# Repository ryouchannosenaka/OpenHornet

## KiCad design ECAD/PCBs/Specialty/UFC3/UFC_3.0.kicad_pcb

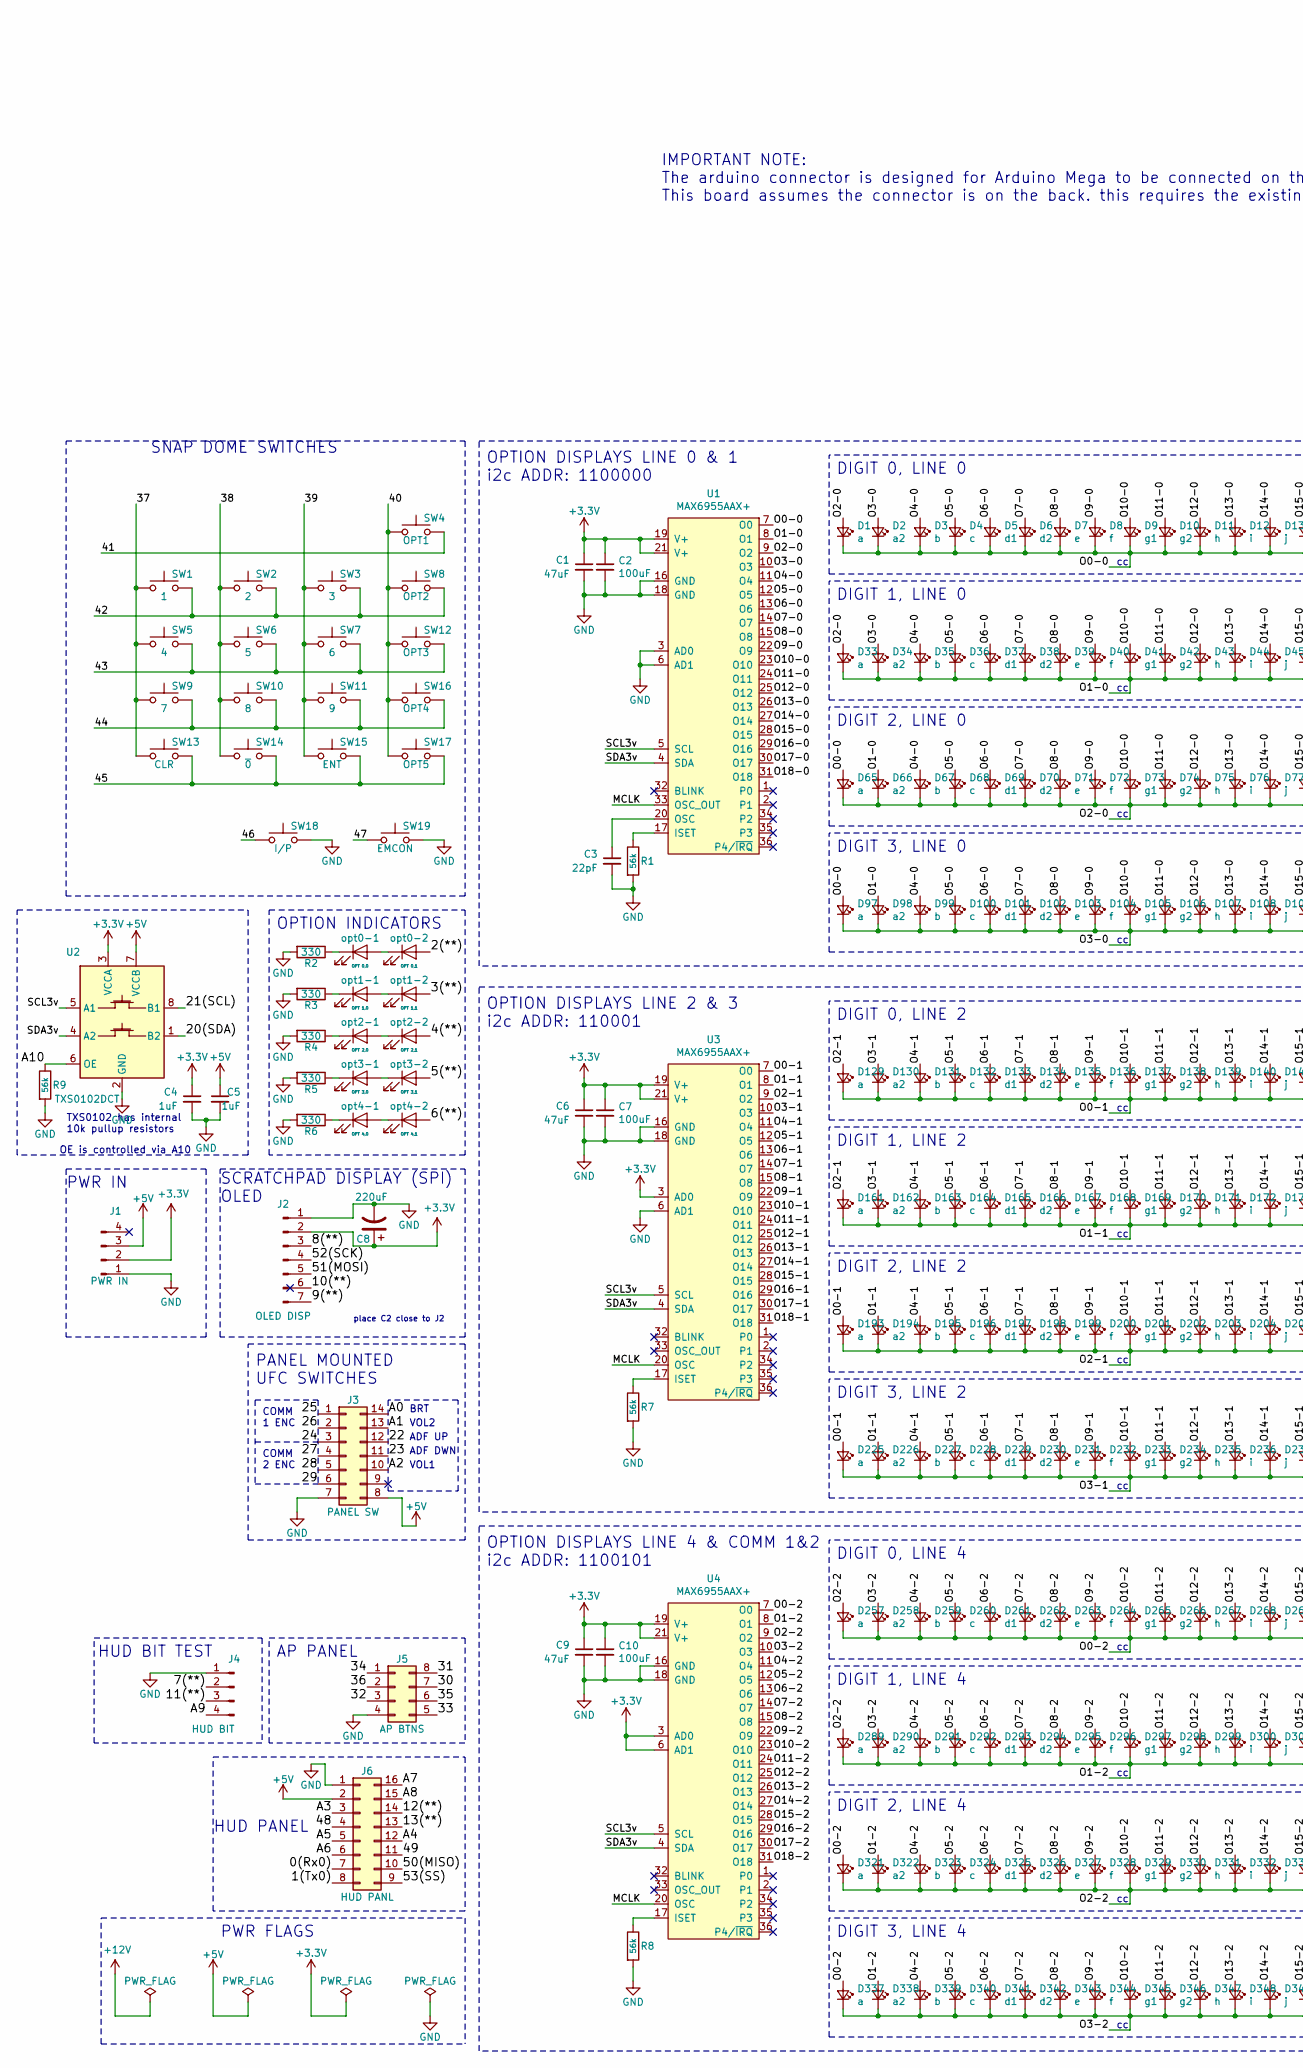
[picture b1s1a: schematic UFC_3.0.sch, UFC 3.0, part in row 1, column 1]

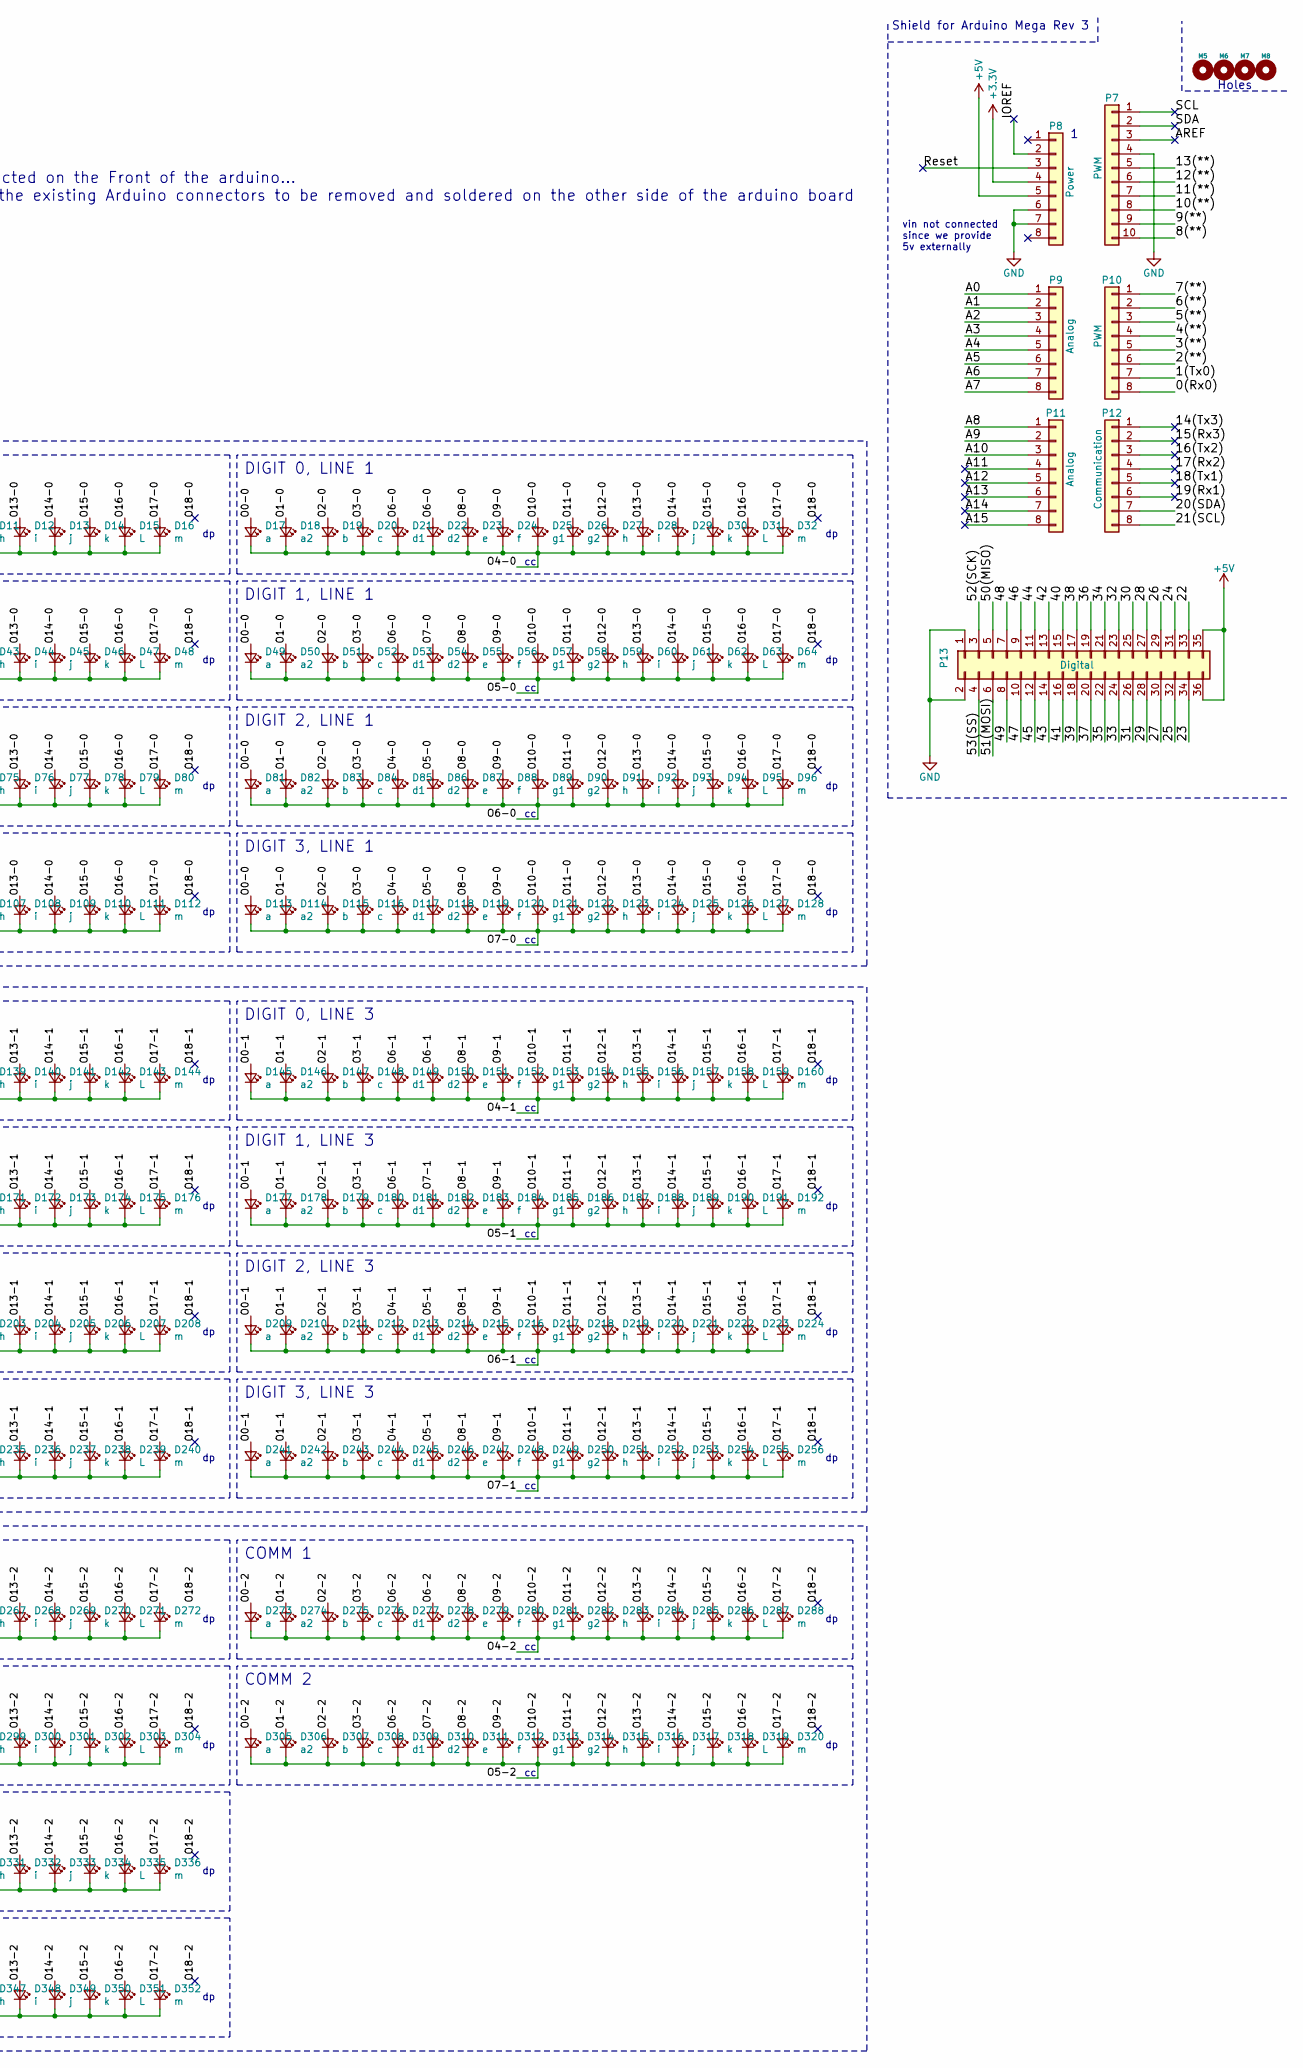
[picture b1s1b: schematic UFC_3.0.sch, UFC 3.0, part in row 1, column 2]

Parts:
C1, C6, C9: 47uF; C_1206_3216Metric
C2, C7, C10: 100uF; C_1206_3216Metric
C3: 22pF; C_0402_1005Metric
C4, C5: 1uF; C_0402_1005Metric
C8: 220uF; CP_Elec_6.3x7.7
D1, D17, D33, D49, D65, D81, D97, D113, D129, D145, D161, D177, D193, D209, D225, D241, D257, D273, D289, D305, D321, D337: a; LED_0402_1005Metric
D2, D18, D34, D50, D66, D82, D98, D114, D130, D146, D162, D178, D194, D210, D226, D242, D258, D274, D290, D306, D322, D338: a2; LED_0402_1005Metric
D3, D19, D35, D51, D67, D83, D99, D115, D131, D147, D163, D179, D195, D211, D227, D243, D259, D275, D291, D307, D323, D339: b; LED_0402_1005Metric
D4, D20, D36, D52, D68, D84, D100, D116, D132, D148, D164, D180, D196, D212, D228, D244, D260, D276, D292, D308, D324, D340: c; LED_0402_1005Metric
D5, D21, D37, D53, D69, D85, D101, D117, D133, D149, D165, D181, D197, D213, D229, D245, D261, D277, D293, D309, D325, D341: d1; LED_0402_1005Metric
D6, D22, D38, D54, D70, D86, D102, D118, D134, D150, D166, D182, D198, D214, D230, D246, D262, D278, D294, D310, D326, D342: d2; LED_0402_1005Metric
D7, D23, D39, D55, D71, D87, D103, D119, D135, D151, D167, D183, D199, D215, D231, D247, D263, D279, D295, D311, D327, D343: e; LED_0402_1005Metric
D8, D24, D40, D56, D72, D88, D104, D120, D136, D152, D168, D184, D200, D216, D232, D248, D264, D280, D296, D312, D328, D344: f; LED_0402_1005Metric
D9, D25, D41, D57, D73, D89, D105, D121, D137, D153, D169, D185, D201, D217, D233, D249, D265, D281, D297, D313, D329, D345: g1; LED_0402_1005Metric
D10, D26, D42, D58, D74, D90, D106, D122, D138, D154, D170, D186, D202, D218, D234, D250, D266, D282, D298, D314, D330, D346: g2; LED_0402_1005Metric
D11, D27, D43, D59, D75, D91, D107, D123, D139, D155, D171, D187, D203, D219, D235, D251, D267, D283, D299, D315, D331, D347: h; LED_0402_1005Metric
D12, D28, D44, D60, D76, D92, D108, D124, D140, D156, D172, D188, D204, D220, D236, D252, D268, D284, D300, D316, D332, D348: i; LED_0402_1005Metric
D13, D29, D45, D61, D77, D93, D109, D125, D141, D157, D173, D189, D205, D221, D237, D253, D269, D285, D301, D317, D333, D349: j; LED_0402_1005Metric
D14, D30, D46, D62, D78, D94, D110, D126, D142, D158, D174, D190, D206, D222, D238, D254, D270, D286, D302, D318, D334, D350: k; LED_0402_1005Metric
D15, D31, D47, D63, D79, D95, D111, D127, D143, D159, D175, D191, D207, D223, D239, D255, D271, D287, D303, D319, D335, D351: L; LED_0402_1005Metric
D16, D32, D48, D64, D80, D96, D112, D128, D144, D160, D176, D192, D208, D224, D240, D256, D272, D288, D304, D320, D336, D352: m; LED_0402_1005Metric
J1: PWR IN; PinHeader_1x04_P2.54mm_Vertical_SMD_Pin1Left
J2: OLED DISP; PinHeader_1x07_P2.54mm_Vertical_SMD_Pin1Left
J3: PANEL SW; PinHeader_2x07_P2.54mm_Vertical_SMD
J4: HUD BIT; PinHeader_1x04_P2.54mm_Vertical_SMD_Pin1Left
J5: AP BTNS; PinHeader_2x04_P2.54mm_Vertical_SMD
J6: HUD PANL; PinHeader_2x08_P2.54mm_Vertical_SMD
M5, M6, M7, M8: mounting hole; MountingHole_2.7mm_M2.5
P7: PWM; PinHeader_1x10_P2.54mm_Vertical_SMD_Pin1Left
P8: Power; PinHeader_1x08_P2.54mm_Vertical_SMD_Pin1Left
P9, P11: Analog; PinHeader_1x08_P2.54mm_Vertical_SMD_Pin1Left
P10: PWM; PinHeader_1x08_P2.54mm_Vertical_SMD_Pin1Left
P12: Communication; PinHeader_1x08_P2.54mm_Vertical_SMD_Pin1Left
P13: Digital; PinHeader_2x18_P2.54mm_Vertical_SMD
R1, R7, R8, R9: 56k; R_0402_1005Metric
R2, R3, R4, R5, R6: 330; R_0402_1005Metric
SW1: 1; SWITCH_SNAP_DOME
SW2: 2; SWITCH_SNAP_DOME
SW3: 3; SWITCH_SNAP_DOME
SW4: OPT1; SWITCH_SNAP_DOME
SW5: 4; SWITCH_SNAP_DOME
SW6: 5; SWITCH_SNAP_DOME
SW7: 6; SWITCH_SNAP_DOME
SW8: OPT2; SWITCH_SNAP_DOME
SW9: 7; SWITCH_SNAP_DOME
SW10: 8; SWITCH_SNAP_DOME
SW11: 9; SWITCH_SNAP_DOME
SW12: OPT3; SWITCH_SNAP_DOME
SW13: CLR; SWITCH_SNAP_DOME
SW14: ~0; SWITCH_SNAP_DOME
SW15: ENT; SWITCH_SNAP_DOME
SW16: OPT4; SWITCH_SNAP_DOME
SW17: OPT5; SWITCH_SNAP_DOME
SW18: I/P; SWITCH_SNAP_DOME
SW19: EMCON; SWITCH_SNAP_DOME
U1, U3, U4: MAX6955AAX+; SSOP-36
U2: TXS0102DCT; SSOP-8_2.95x2.8mm_P0.65mm
opt0-1: OPT 0,0; LED_0402_1005Metric
opt0-2: OPT 0,1; LED_0402_1005Metric
opt1-1: OPT 1,0; LED_0402_1005Metric
opt1-2: OPT 1,1; LED_0402_1005Metric
opt2-1: OPT 2,0; LED_0402_1005Metric
opt2-2: OPT 2,1; LED_0402_1005Metric
opt3-1: OPT 3,0; LED_0402_1005Metric
opt3-2: OPT 3,1; LED_0402_1005Metric
opt4-1: OPT 4,0; LED_0402_1005Metric
opt4-2: OPT 4,1; LED_0402_1005Metric

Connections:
+3V3: C1.1, C2.1, C4.1, C6.1, C7.1, C8.1, C9.1, C10.1, J1.2, J2.2, P8.4, U1.19 (V+), U1.21 (V+), U2.3 (VCCA), U3.3 (AD0), U3.19 (V+), U3.21 (V+), U4.3 (AD0), U4.6 (AD1), U4.19 (V+), U4.21 (V+)
+5V: C5.1, J1.3, J3.8, J6.2, P8.5, P13.35, P13.36, U2.7 (VCCB)
/0(Rx0): J6.7, P10.8
/1(Tx0): J6.8, P10.7
/2(**): P10.6, opt0-2.2 (A)
/3(**): P10.5, opt1-2.2 (A)
/4(**): P10.4, opt2-2.2 (A)
/5(**): P10.3, opt3-2.2 (A)
/6(**): P10.2, opt4-2.2 (A)
/7(**): J4.2, P10.1
/8(**): J2.3, P7.10
/9(**): J2.7, P7.9
/10(**): J2.6, P7.8
/11(**): J4.3, P7.7
/12(**): J6.14, P7.6
/13(**): J6.13, P7.5
/14(Tx3): P12.1
/15(Rx3): P12.2
/16(Tx2): P12.3
/17(Rx2): P12.4
/18(Tx1): P12.5
/19(Rx1): P12.6
/20(SDA): P12.7, U2.1 (B2)
/21(SCL): P12.8, U2.8 (B1)
/22: J3.12, P13.33
/23: J3.11, P13.34
/24: J3.3, P13.31
/25: J3.1, P13.32
/26: J3.2, P13.29
/27: J3.4, P13.30
/28: J3.5, P13.27
/29: J3.6, P13.28
/30: J5.7, P13.25
/31: J5.8, P13.26
/32: J5.3, P13.23
/33: J5.5, P13.24
/34: J5.1, P13.21
/35: J5.6, P13.22
/36: J5.2, P13.19
/37: P13.20, SW1.1, SW5.1, SW9.1, SW13.1
/38: P13.17, SW2.1, SW6.1, SW10.1, SW14.1
/39: P13.18, SW3.1, SW7.1, SW11.1, SW15.1
/40: P13.15, SW4.1, SW8.1, SW12.1, SW16.1, SW17.1
/41: P13.16, SW4.2
/42: P13.13, SW1.2, SW2.2, SW3.2, SW8.2
/43: P13.14, SW5.2, SW6.2, SW7.2, SW12.2
/44: P13.11, SW9.2, SW10.2, SW11.2, SW16.2
/45: P13.12, SW13.2, SW14.2, SW15.2, SW17.2
/46: P13.9, SW18.1
/47: P13.10, SW19.1
/48: J6.4, P13.7
/49: J6.11, P13.8
/50(MISO): J6.10, P13.5
/51(MOSI): J2.5, P13.6
/52(SCK): J2.4, P13.3
/53(SS): J6.9, P13.4
/A0: J3.14, P9.1
/A1: J3.13, P9.2
/A2: J3.10, P9.3
/A3: J6.3, P9.4
/A4: J6.12, P9.5
/A5: J6.5, P9.6
/A6: J6.6, P9.7
/A7: J6.16, P9.8
/A8: J6.15, P11.1
/A9: J4.4, P11.2
/A10: P11.3, R9.1, U2.6 (OE)
/A11: P11.4
/A12: P11.5
/A13: P11.6
/A14: P11.7
/A15: P11.8
/AREF: P7.3
/IOREF: P8.2
/MCLK: U1.33 (OSC_OUT), U3.20 (OSC), U4.20 (OSC)
/O0-0: D1.1 (K), D2.1 (K), D3.1 (K), D4.1 (K), D5.1 (K), D6.1 (K), D7.1 (K), D8.1 (K), D9.1 (K), D10.1 (K), D11.1 (K), D12.1 (K), D13.1 (K), D14.1 (K), D15.1 (K), D16.1 (K), D17.2 (A), D49.2 (A), D65.2 (A), D81.2 (A), D97.2 (A), D113.2 (A), U1.7 (O0)
/O0-1: D129.1 (K), D130.1 (K), D131.1 (K), D132.1 (K), D133.1 (K), D134.1 (K), D135.1 (K), D136.1 (K), D137.1 (K), D138.1 (K), D139.1 (K), D140.1 (K), D141.1 (K), D142.1 (K), D143.1 (K), D144.1 (K), D145.2 (A), D177.2 (A), D193.2 (A), D209.2 (A), D225.2 (A), D241.2 (A), U3.7 (O0)
/O0-2: D257.1 (K), D258.1 (K), D259.1 (K), D260.1 (K), D261.1 (K), D262.1 (K), D263.1 (K), D264.1 (K), D265.1 (K), D266.1 (K), D267.1 (K), D268.1 (K), D269.1 (K), D270.1 (K), D271.1 (K), D272.1 (K), D273.2 (A), D305.2 (A), D321.2 (A), D337.2 (A), U4.7 (O0)
/O1-0: D18.2 (A), D33.1 (K), D34.1 (K), D35.1 (K), D36.1 (K), D37.1 (K), D38.1 (K), D39.1 (K), D40.1 (K), D41.1 (K), D42.1 (K), D43.1 (K), D44.1 (K), D45.1 (K), D46.1 (K), D47.1 (K), D48.1 (K), D50.2 (A), D66.2 (A), D82.2 (A), D98.2 (A), D114.2 (A), U1.8 (O1)
/O1-1: D146.2 (A), D161.1 (K), D162.1 (K), D163.1 (K), D164.1 (K), D165.1 (K), D166.1 (K), D167.1 (K), D168.1 (K), D169.1 (K), D170.1 (K), D171.1 (K), D172.1 (K), D173.1 (K), D174.1 (K), D175.1 (K), D176.1 (K), D178.2 (A), D194.2 (A), D210.2 (A), D226.2 (A), D242.2 (A), U3.8 (O1)
/O1-2: D274.2 (A), D289.1 (K), D290.1 (K), D291.1 (K), D292.1 (K), D293.1 (K), D294.1 (K), D295.1 (K), D296.1 (K), D297.1 (K), D298.1 (K), D299.1 (K), D300.1 (K), D301.1 (K), D302.1 (K), D303.1 (K), D304.1 (K), D306.2 (A), D322.2 (A), D338.2 (A), U4.8 (O1)
/O2-0: D1.2 (A), D19.2 (A), D33.2 (A), D51.2 (A), D65.1 (K), D66.1 (K), D67.1 (K), D68.1 (K), D69.1 (K), D70.1 (K), D71.1 (K), D72.1 (K), D73.1 (K), D74.1 (K), D75.1 (K), D76.1 (K), D77.1 (K), D78.1 (K), D79.1 (K), D80.1 (K), D83.2 (A), D115.2 (A), U1.9 (O2)
/O2-1: D129.2 (A), D147.2 (A), D161.2 (A), D179.2 (A), D193.1 (K), D194.1 (K), D195.1 (K), D196.1 (K), D197.1 (K), D198.1 (K), D199.1 (K), D200.1 (K), D201.1 (K), D202.1 (K), D203.1 (K), D204.1 (K), D205.1 (K), D206.1 (K), D207.1 (K), D208.1 (K), D211.2 (A), D243.2 (A), U3.9 (O2)
/O2-2: D257.2 (A), D275.2 (A), D289.2 (A), D307.2 (A), D321.1 (K), D322.1 (K), D323.1 (K), D324.1 (K), D325.1 (K), D326.1 (K), D327.1 (K), D328.1 (K), D329.1 (K), D330.1 (K), D331.1 (K), D332.1 (K), D333.1 (K), D334.1 (K), D335.1 (K), D336.1 (K), U4.9 (O2)
/O3-0: D2.2 (A), D20.2 (A), D34.2 (A), D52.2 (A), D84.2 (A), D97.1 (K), D98.1 (K), D99.1 (K), D100.1 (K), D101.1 (K), D102.1 (K), D103.1 (K), D104.1 (K), D105.1 (K), D106.1 (K), D107.1 (K), D108.1 (K), D109.1 (K), D110.1 (K), D111.1 (K), D112.1 (K), D116.2 (A), U1.10 (O3)
/O3-1: D130.2 (A), D148.2 (A), D162.2 (A), D180.2 (A), D212.2 (A), D225.1 (K), D226.1 (K), D227.1 (K), D228.1 (K), D229.1 (K), D230.1 (K), D231.1 (K), D232.1 (K), D233.1 (K), D234.1 (K), D235.1 (K), D236.1 (K), D237.1 (K), D238.1 (K), D239.1 (K), D240.1 (K), D244.2 (A), U3.10 (O3)
/O3-2: D258.2 (A), D276.2 (A), D290.2 (A), D308.2 (A), D337.1 (K), D338.1 (K), D339.1 (K), D340.1 (K), D341.1 (K), D342.1 (K), D343.1 (K), D344.1 (K), D345.1 (K), D346.1 (K), D347.1 (K), D348.1 (K), D349.1 (K), D350.1 (K), D351.1 (K), D352.1 (K), U4.10 (O3)
/O4-0: D3.2 (A), D17.1 (K), D18.1 (K), D19.1 (K), D20.1 (K), D21.1 (K), D22.1 (K), D23.1 (K), D24.1 (K), D25.1 (K), D26.1 (K), D27.1 (K), D28.1 (K), D29.1 (K), D30.1 (K), D31.1 (K), D32.1 (K), D35.2 (A), D67.2 (A), D85.2 (A), D99.2 (A), D117.2 (A), U1.11 (O4)
/O4-1: D131.2 (A), D145.1 (K), D146.1 (K), D147.1 (K), D148.1 (K), D149.1 (K), D150.1 (K), D151.1 (K), D152.1 (K), D153.1 (K), D154.1 (K), D155.1 (K), D156.1 (K), D157.1 (K), D158.1 (K), D159.1 (K), D160.1 (K), D163.2 (A), D195.2 (A), D213.2 (A), D227.2 (A), D245.2 (A), U3.11 (O4)
/O4-2: D259.2 (A), D273.1 (K), D274.1 (K), D275.1 (K), D276.1 (K), D277.1 (K), D278.1 (K), D279.1 (K), D280.1 (K), D281.1 (K), D282.1 (K), D283.1 (K), D284.1 (K), D285.1 (K), D286.1 (K), D287.1 (K), D288.1 (K), D291.2 (A), D323.2 (A), D339.2 (A), U4.11 (O4)
/O5-0: D4.2 (A), D36.2 (A), D49.1 (K), D50.1 (K), D51.1 (K), D52.1 (K), D53.1 (K), D54.1 (K), D55.1 (K), D56.1 (K), D57.1 (K), D58.1 (K), D59.1 (K), D60.1 (K), D61.1 (K), D62.1 (K), D63.1 (K), D64.1 (K), D68.2 (A), D86.2 (A), D100.2 (A), D118.2 (A), U1.12 (O5)
/O5-1: D132.2 (A), D164.2 (A), D177.1 (K), D178.1 (K), D179.1 (K), D180.1 (K), D181.1 (K), D182.1 (K), D183.1 (K), D184.1 (K), D185.1 (K), D186.1 (K), D187.1 (K), D188.1 (K), D189.1 (K), D190.1 (K), D191.1 (K), D192.1 (K), D196.2 (A), D214.2 (A), D228.2 (A), D246.2 (A), U3.12 (O5)
/O5-2: D260.2 (A), D292.2 (A), D305.1 (K), D306.1 (K), D307.1 (K), D308.1 (K), D309.1 (K), D310.1 (K), D311.1 (K), D312.1 (K), D313.1 (K), D314.1 (K), D315.1 (K), D316.1 (K), D317.1 (K), D318.1 (K), D319.1 (K), D320.1 (K), D324.2 (A), D340.2 (A), U4.12 (O5)
/O6-0: D5.2 (A), D21.2 (A), D22.2 (A), D37.2 (A), D53.2 (A), D69.2 (A), D81.1 (K), D82.1 (K), D83.1 (K), D84.1 (K), D85.1 (K), D86.1 (K), D87.1 (K), D88.1 (K), D89.1 (K), D90.1 (K), D91.1 (K), D92.1 (K), D93.1 (K), D94.1 (K), D95.1 (K), D96.1 (K), D101.2 (A), U1.13 (O6)
/O6-1: D133.2 (A), D149.2 (A), D150.2 (A), D165.2 (A), D181.2 (A), D197.2 (A), D209.1 (K), D210.1 (K), D211.1 (K), D212.1 (K), D213.1 (K), D214.1 (K), D215.1 (K), D216.1 (K), D217.1 (K), D218.1 (K), D219.1 (K), D220.1 (K), D221.1 (K), D222.1 (K), D223.1 (K), D224.1 (K), D229.2 (A), U3.13 (O6)
/O6-2: D261.2 (A), D277.2 (A), D278.2 (A), D293.2 (A), D309.2 (A), D325.2 (A), D341.2 (A), U4.13 (O6)
/O7-0: D6.2 (A), D38.2 (A), D54.2 (A), D70.2 (A), D102.2 (A), D113.1 (K), D114.1 (K), D115.1 (K), D116.1 (K), D117.1 (K), D118.1 (K), D119.1 (K), D120.1 (K), D121.1 (K), D122.1 (K), D123.1 (K), D124.1 (K), D125.1 (K), D126.1 (K), D127.1 (K), D128.1 (K), U1.14 (O7)
/O7-1: D134.2 (A), D166.2 (A), D182.2 (A), D198.2 (A), D230.2 (A), D241.1 (K), D242.1 (K), D243.1 (K), D244.1 (K), D245.1 (K), D246.1 (K), D247.1 (K), D248.1 (K), D249.1 (K), D250.1 (K), D251.1 (K), D252.1 (K), D253.1 (K), D254.1 (K), D255.1 (K), D256.1 (K), U3.14 (O7)
/O7-2: D262.2 (A), D294.2 (A), D310.2 (A), D326.2 (A), D342.2 (A), U4.14 (O7)
/O8-0: D7.2 (A), D23.2 (A), D39.2 (A), D55.2 (A), D71.2 (A), D87.2 (A), D103.2 (A), D119.2 (A), U1.15 (O8)
/O8-1: D135.2 (A), D151.2 (A), D167.2 (A), D183.2 (A), D199.2 (A), D215.2 (A), D231.2 (A), D247.2 (A), U3.15 (O8)
/O8-2: D263.2 (A), D279.2 (A), D295.2 (A), D311.2 (A), D327.2 (A), D343.2 (A), U4.15 (O8)
/O9-0: D8.2 (A), D24.2 (A), D40.2 (A), D56.2 (A), D72.2 (A), D88.2 (A), D104.2 (A), D120.2 (A), U1.22 (O9)
/O9-1: D136.2 (A), D152.2 (A), D168.2 (A), D184.2 (A), D200.2 (A), D216.2 (A), D232.2 (A), D248.2 (A), U3.22 (O9)
/O9-2: D264.2 (A), D280.2 (A), D296.2 (A), D312.2 (A), D328.2 (A), D344.2 (A), U4.22 (O9)
/O10-0: D9.2 (A), D25.2 (A), D41.2 (A), D57.2 (A), D73.2 (A), D89.2 (A), D105.2 (A), D121.2 (A), U1.23 (O10)
/O10-1: D137.2 (A), D153.2 (A), D169.2 (A), D185.2 (A), D201.2 (A), D217.2 (A), D233.2 (A), D249.2 (A), U3.23 (O10)
/O10-2: D265.2 (A), D281.2 (A), D297.2 (A), D313.2 (A), D329.2 (A), D345.2 (A), U4.23 (O10)
/O11-0: D10.2 (A), D26.2 (A), D42.2 (A), D58.2 (A), D74.2 (A), D90.2 (A), D106.2 (A), D122.2 (A), U1.24 (O11)
/O11-1: D138.2 (A), D154.2 (A), D170.2 (A), D186.2 (A), D202.2 (A), D218.2 (A), D234.2 (A), D250.2 (A), U3.24 (O11)
/O11-2: D266.2 (A), D282.2 (A), D298.2 (A), D314.2 (A), D330.2 (A), D346.2 (A), U4.24 (O11)
/O12-0: D11.2 (A), D27.2 (A), D43.2 (A), D59.2 (A), D75.2 (A), D91.2 (A), D107.2 (A), D123.2 (A), U1.25 (O12)
/O12-1: D139.2 (A), D155.2 (A), D171.2 (A), D187.2 (A), D203.2 (A), D219.2 (A), D235.2 (A), D251.2 (A), U3.25 (O12)
/O12-2: D267.2 (A), D283.2 (A), D299.2 (A), D315.2 (A), D331.2 (A), D347.2 (A), U4.25 (O12)
/O13-0: D12.2 (A), D28.2 (A), D44.2 (A), D60.2 (A), D76.2 (A), D92.2 (A), D108.2 (A), D124.2 (A), U1.26 (O13)
/O13-1: D140.2 (A), D156.2 (A), D172.2 (A), D188.2 (A), D204.2 (A), D220.2 (A), D236.2 (A), D252.2 (A), U3.26 (O13)
/O13-2: D268.2 (A), D284.2 (A), D300.2 (A), D316.2 (A), D332.2 (A), D348.2 (A), U4.26 (O13)
/O14-0: D13.2 (A), D29.2 (A), D45.2 (A), D61.2 (A), D77.2 (A), D93.2 (A), D109.2 (A), D125.2 (A), U1.27 (O14)
/O14-1: D141.2 (A), D157.2 (A), D173.2 (A), D189.2 (A), D205.2 (A), D221.2 (A), D237.2 (A), D253.2 (A), U3.27 (O14)
/O14-2: D269.2 (A), D285.2 (A), D301.2 (A), D317.2 (A), D333.2 (A), D349.2 (A), U4.27 (O14)
/O15-0: D14.2 (A), D30.2 (A), D46.2 (A), D62.2 (A), D78.2 (A), D94.2 (A), D110.2 (A), D126.2 (A), U1.28 (O15)
/O15-1: D142.2 (A), D158.2 (A), D174.2 (A), D190.2 (A), D206.2 (A), D222.2 (A), D238.2 (A), D254.2 (A), U3.28 (O15)
/O15-2: D270.2 (A), D286.2 (A), D302.2 (A), D318.2 (A), D334.2 (A), D350.2 (A), U4.28 (O15)
/O16-0: D15.2 (A), D31.2 (A), D47.2 (A), D63.2 (A), D79.2 (A), D95.2 (A), D111.2 (A), D127.2 (A), U1.29 (O16)
/O16-1: D143.2 (A), D159.2 (A), D175.2 (A), D191.2 (A), D207.2 (A), D223.2 (A), D239.2 (A), D255.2 (A), U3.29 (O16)
/O16-2: D271.2 (A), D287.2 (A), D303.2 (A), D319.2 (A), D335.2 (A), D351.2 (A), U4.29 (O16)
/O17-0: D16.2 (A), D32.2 (A), D48.2 (A), D64.2 (A), D80.2 (A), D96.2 (A), D112.2 (A), D128.2 (A), U1.30 (O17)
/O17-1: D144.2 (A), D160.2 (A), D176.2 (A), D192.2 (A), D208.2 (A), D224.2 (A), D240.2 (A), D256.2 (A), U3.30 (O17)
/O17-2: D272.2 (A), D288.2 (A), D304.2 (A), D320.2 (A), D336.2 (A), D352.2 (A), U4.30 (O17)
/O18-0: U1.31 (O18)
/O18-1: U3.31 (O18)
/O18-2: U4.31 (O18)
/Reset: P8.3
/SCL: P7.1
/SCL3v: U1.5 (SCL), U2.5 (A1), U3.5 (SCL), U4.5 (SCL)
/SDA: P7.2
/SDA3v: U1.4 (SDA), U2.4 (A2), U3.4 (SDA), U4.4 (SDA)
GND: C1.2, C2.2, C3.2, C4.2, C5.2, C6.2, C7.2, C8.2, C9.2, C10.2, J1.1, J2.1, J3.7, J4.1, J5.4, J6.1, P7.4, P8.6, P8.7, P13.1, P13.2, R1.2, R2.2, R3.2, R4.2, R5.2, R6.2, R7.2, R8.2, R9.2, SW18.2, SW19.2, U1.3 (AD0), U1.6 (AD1), U1.16 (GND), U1.18 (GND), U2.2 (GND), U3.6 (AD1), U3.16 (GND), U3.18 (GND), U4.16 (GND), U4.18 (GND)
unnamed: C3.1, U1.20 (OSC)
unnamed: R1.1, U1.17 (ISET)
unnamed: R2.1, opt0-1.1 (K)
unnamed: R3.1, opt1-1.1 (K)
unnamed: R4.1, opt2-1.1 (K)
unnamed: R5.1, opt3-1.1 (K)
unnamed: R6.1, opt4-1.1 (K)
unnamed: R7.1, U3.17 (ISET)
unnamed: R8.1, U4.17 (ISET)
unnamed: opt0-1.2 (A), opt0-2.1 (K)
unnamed: opt1-1.2 (A), opt1-2.1 (K)
unnamed: opt2-1.2 (A), opt2-2.1 (K)
unnamed: opt3-1.2 (A), opt3-2.1 (K)
unnamed: opt4-1.2 (A), opt4-2.1 (K)

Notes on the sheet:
Shield for Arduino Mega Rev 3
Holes
PANEL MOUNTED UFC SWITCHES
PWR IN
SCRATCHPAD DISPLAY (SPI) OLED
AP PANEL
HUD PANEL
HUD BIT TEST
PWR FLAGS
place C2 close to J2
SNAP DOME SWITCHES
OPTION DISPLAYS LINE 0 & 1 i2c ADDR: 1100000
OPTION INDICATORS
OPTION DISPLAYS LINE 2 & 3 i2c ADDR: 110001
vin not connected since we provide 5v externally
TXS0102 has internal 10k pullup resistors
COMM 1 ENC
COMM 2 ENC
BRT
VOL2
VOL1
ADF UP
ADF DWN
COMM 1
COMM 2
OPTION DISPLAYS LINE 4 & COMM 1&2 i2c ADDR: 1100101
DIGIT 0, LINE 4
DIGIT 1, LINE 4
DIGIT 2, LINE 4
DIGIT 3, LINE 4
DIGIT 0, LINE 3
DIGIT 0, LINE 2
DIGIT 1, LINE 2
DIGIT 2, LINE 2
DIGIT 3, LINE 2
DIGIT 1, LINE 3
DIGIT 2, LINE 3
DIGIT 3, LINE 3
DIGIT 0, LINE 1
DIGIT 0, LINE 0

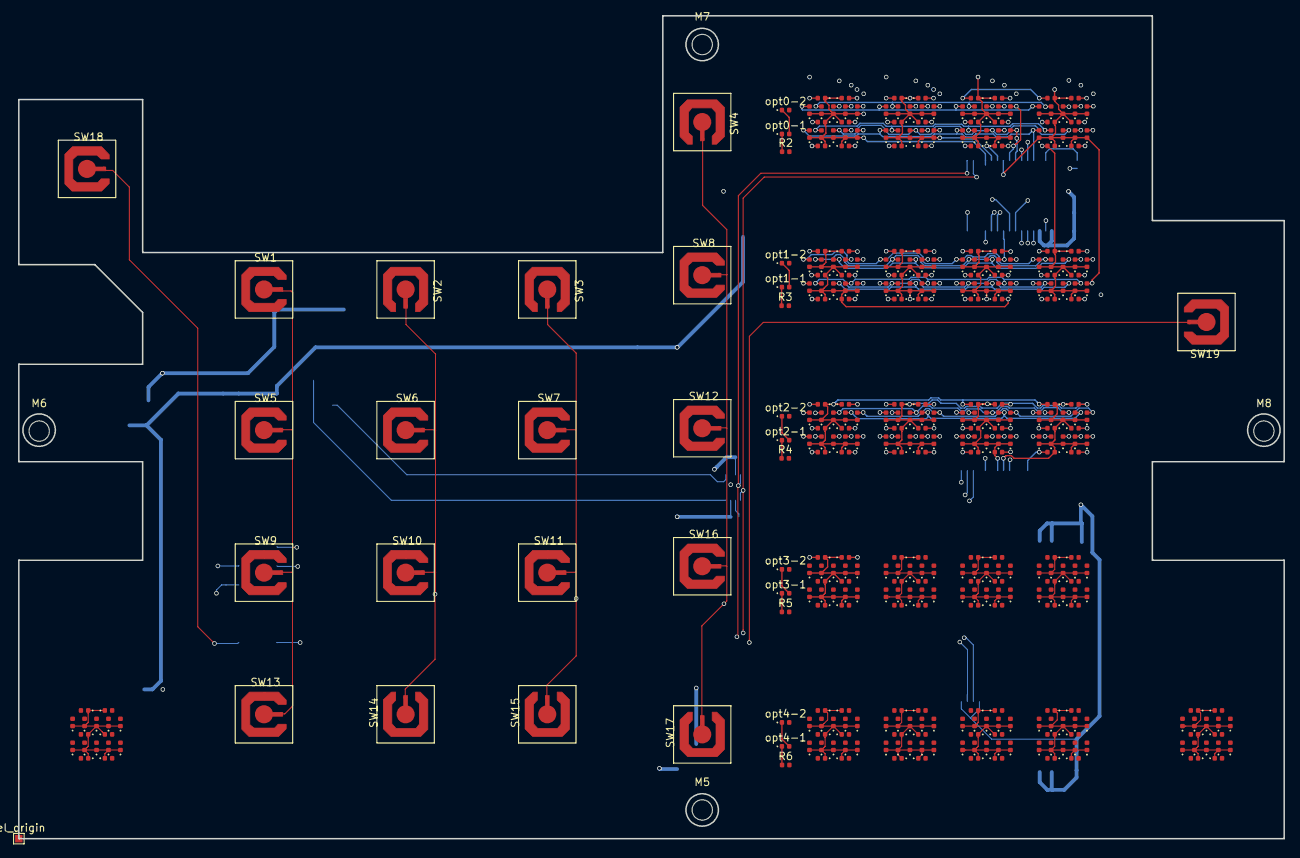
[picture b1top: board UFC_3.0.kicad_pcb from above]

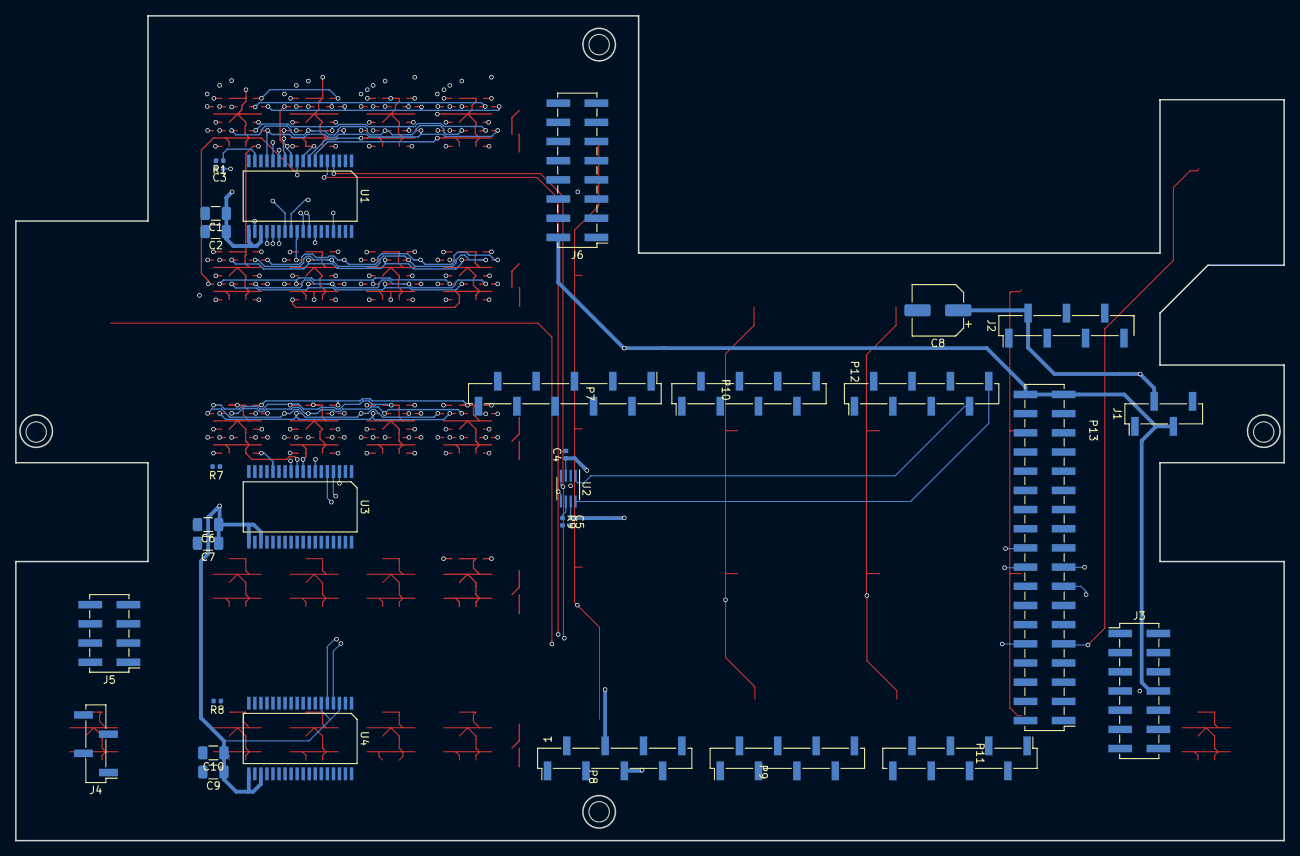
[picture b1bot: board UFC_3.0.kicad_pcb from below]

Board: 4 copper layers, 168.0 x 109.2 mm, 422 parts (31 on the bottom side), 133 nets.

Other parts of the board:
rel_origin: TestPoint_Pad_1.0x1.0mm

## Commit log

2019-11-22 Clean gh-pages branch
2019-11-22 Removed .DS_Store
2019-11-22 Deploy code docs to GitHub Pages Travis build: 2
    Commit: 61a8155cd6c9ae6c0e3081eb8e27eea6d94e9289
2019-11-22 Deploy code docs to GitHub Pages Travis build: 4
    Commit: 8635e0b0fb9bcbec6488768515a3b42fa4c964cb
2019-11-24 Deploy code docs to GitHub Pages Travis build: 6
    Commit: cbb4e7d4324b8377ecf7254bef07ebba8f5375c3
2019-11-29 Deploy code docs to GitHub Pages Travis build: 8
    Commit: 84d7b67b8bc8f993b1584f4438c80d3e0c7d22c8
2019-12-17 Deploy code docs to GitHub Pages Travis build: 12
    Commit: a054a0d3dbd982bf4f8d0da91e40e7af39b49b87
2019-12-24 Deploy code docs to GitHub Pages Travis build: 14
    Commit: e11fbd1b72adbcb1b2def59ddc333c8ffd791420
2020-05-07 WIP
    Trimmed rails, need to attach rockets to side of rails, and continue rest of redesign work. Paused pending better seat data.
2020-05-08 Reduced thickness of LH seat controls.
    Reduced from 1.25 to .6875.
2020-05-08 Repositioned Parachute Deployment Rocket
2020-06-30 temporary commit, this commit contains a partial version of the routing for UFC v3. along this commit I have added a python script to place the components based on the location listed on a csv file
2020-07-06 Initial Commit
    Seat Bucket WIP.
2020-07-10 WIP Seat Bucket
    Work on Manual Override Handle Continued. Changed to clevis pins, added mechanical linkage. Need to add switch, switch housing, and connecting rod guard.
2020-07-13 Seat Bucket WIP
2020-09-25 Seat WIP
2020-09-26 Seat arming lever mechanism
    Conceptual checkpoint - revert to here if needed.
2020-09-26 Seat Arming Lever Linkage Mechanism Complete
    Need to add detent to seat arming lever, and cable passthrough for switch.
2020-09-26 Seat Bucket (Concept) Complete
    Finished seat bucket.
    Needs assembly hardware (MDF screws) and cosmetics done.
2020-10-08 temp commit
    temp commit
2020-11-02 Revert "Create debug.log"
    This reverts commit 57c0ab68fd2acec2fd7b9771f37a20a09a805d3d.
2020-11-02 Revert "Update Buttons_DDI.pro"
    This reverts commit e0f2a090f9d3fd2e835338795bc42ed46c0a9f7b.
